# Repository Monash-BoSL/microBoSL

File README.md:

# microBoSL
This is a repository for the microBoSL motor controller

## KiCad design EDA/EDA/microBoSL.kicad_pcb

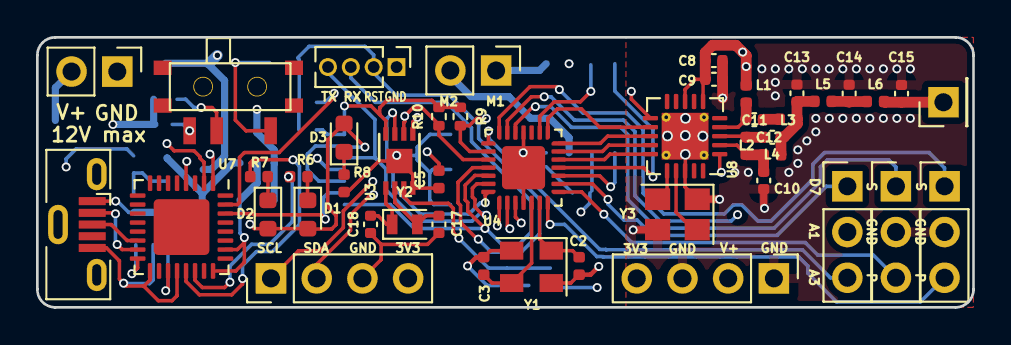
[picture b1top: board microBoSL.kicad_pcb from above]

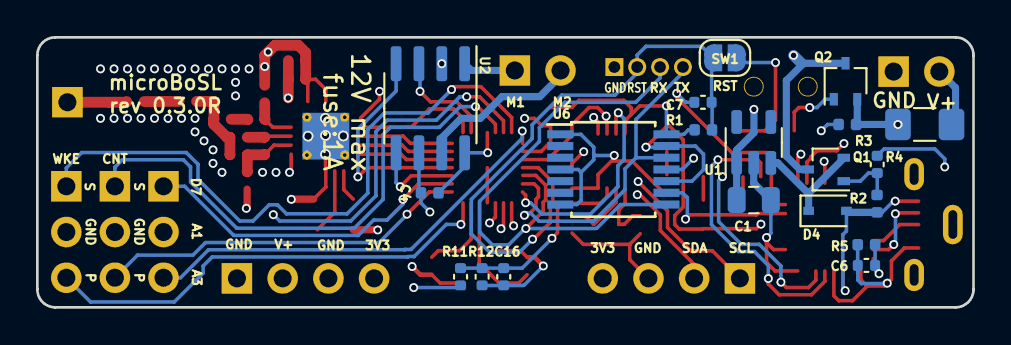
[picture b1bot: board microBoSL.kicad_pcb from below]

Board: 4 copper layers, 52.0 x 15.0 mm, 65 parts (20 on the bottom side), 58 nets.

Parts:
AE1: Antenna; PinHeader_1x01_P2.54mm_Vertical
C1: 2.2 μF; C_0805_2012Metric
C2, C3: 22 pF; C_0402_1005Metric
C4, C5, C6, C7, C9, C16: 100 nF; C_0402_1005Metric
C8: 100 pF; C_0402_1005Metric
C10, C12: 5.1 pF; C_0402_1005Metric
C11: 6.8 pF; C_0402_1005Metric
C13: 12 pF; C_0402_1005Metric
C14: 18 pF; C_0402_1005Metric
C15: 9.1 pF; C_0402_1005Metric
C17, C18: 15 pF; C_0402_1005Metric
D1, D2, D3: LED; LED_0603_1608Metric
D4: CUS08F30,H3F; D_SOD-323
F1: 1A; Fuse_1206_3216Metric_Pad1.42x1.75mm_HandSolder
J1, J4: Conn_01x04; PinHeader_1x04_P2.54mm_Vertical
J2, J6, J7: Conn_01x03; PinHeader_1x03_P2.54mm_Vertical
J3: Conn_01x04; PinHeader_1x04_P1.27mm_Vertical
J5: Conn_01x02; PinHeader_1x02_P2.54mm_Vertical
J8: USB_B_Micro; USB_Micro-B_Molex-105133-0001
J9: MOTOR_OUT; PinHeader_1x02_P2.54mm_Vertical
L1: 220 nH; L_0402_1005Metric
L2: 68 nH; L_0402_1005Metric
L3: 24 nH; L_0402_1005Metric
L4: 27 nH; L_0402_1005Metric
L5, L6: 12 nH; L_0402_1005Metric
Q1, Q2: DMP2165UW; SOT-323_SC-70
R1, R2, R3, R5, R9, R10: 10 kΩ; R_0402_1005Metric
R4, R11, R12: 4.7 MΩ; C_0402_1005Metric
R6, R7, R8: 3.3 kΩ; R_0402_1005Metric
SW1: RST; SolderJumper-2_P1.3mm_Open_RoundedPad1.0x1.5mm
SW2: EG1215AA
U1: TPS709A33DBVT; SOT-23-5
U2: ZXBM5210-S; SOIC-8_3.9x4.9mm_P1.27mm
U3: MCP7940N-xMNY; DFN-8-1EP_3x2mm_P0.5mm_EP1.36x1.46mm
U4: ATmega328-MMH; QFN-28-1EP_4x4mm_P0.45mm_EP2.4x2.4mm
U6: 74HC126PW-Q100; TSSOP-14_4.4x5mm_P0.65mm
U7: FT232RQ; QFN-32-1EP_5x5mm_P0.5mm_EP3.1x3.1mm
U8: Si4463; QFN-20-1EP_4x4mm_P0.5mm_EP2.6x2.6mm_ThermalVias
Y1: 8MHz; Crystal_SMD_EuroQuartz_MT-4Pin_3.2x2.5mm
Y2: 32.768 kHz; Crystal_SMD_2012-2Pin_2.0x1.2mm
Y3: 30 MHz; Crystal_SMD_Abracon_ABM8G-4Pin_3.2x2.5mm

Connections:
A1: J2.2, U4.20 (PC1)
A3: J2.3, U4.22 (PC3)
AND_RX: U6.9 (A3), U7.30 (TXD)
AND_TX: U6.11 (Y4), U7.2 (RXD)
D7: J2.1, U4.9 (PD7)
EN_RADIO: U4.2 (PD4), U8.1 (SDN)
GND: C1.2, C2.1, C3.1, C4.1, C5.2, C6.2, C8.2, C9.2, C10.2, C13.2, C14.2, C15.2, C16.2, C17.1, C18.1, J1.3, J3.1, J4.1, J4.3, J5.1, J6.2, J7.2, J8.5 (GND), R4.1, R5.2, R8.2, R12.2, SW1.1, SW2.1 (A), U1.2 (GND), U2.8 (GND), U3.4 (VSS), U3.9 (EP), U4.4 (GND), U4.18 (GND), U4.29 (GND), U6.1 (OE1), U6.4 (OE2), U6.7 (GND), U7.4 (GND), U7.17 (GND), U7.20 (GND), U7.24 (AGND), U7.26 (TEST), U8.18 (GND), U8.21 (GND), Y1.2, Y1.4, Y3.1, Y3.3
Hall_CNT_P: J6.3, U4.8 (PD6)
Hall_CNT_S: J6.1, U4.19 (PC0)
Hall_WKE_P: J7.3, U4.7 (PD5)
Hall_WKE_S: J7.1, U4.21 (PC2)
I_RADIO: U4.1 (PD3), U8.11 (~IRQ)
MFWD: U2.4 (FWD), U4.11 (PB1)
MISO: U4.14 (PB4), U8.13 (SDO)
MOSI: U4.13 (PB3), U8.14 (SDI)
MREV: U2.5 (REV), U4.10 (PB0)
unnamed: AE1.1 (A), C15.1, L6.2
unnamed: C2.2, U4.6 (XTAL2/PB7), Y1.1
unnamed: C3.2, U4.5 (XTAL1/PB6), Y1.3
unnamed: C7.2, U7.31 (DTR)
unnamed: C10.1, L2.1, L4.1, U8.2 (RXp)
unnamed: C11.1, L3.1
unnamed: C11.2, L1.2, U8.4 (TX)
unnamed: C12.1, C13.1, L3.2, L4.2, L5.1
unnamed: C12.2, L2.2, U8.3 (RXn)
unnamed: C14.1, L5.2, L6.1
unnamed: C16.1, R11.2, R12.1, U3.3 (VBAT)
unnamed: C17.2, U3.2 (X2), Y2.2
unnamed: C18.2, U3.1 (X1), Y2.1
unnamed: D1.1 (K), R6.1
unnamed: D2.1 (K), R7.1
unnamed: D3.1 (K), R8.1
unnamed: D4.1 (K), Q1.2 (S), U1.3 (IN)
unnamed: F1.2, J5.2
unnamed: J9.1, U2.1 (OUT1)
unnamed: J9.2, U2.7 (OUT2)
unnamed: Q1.1 (G), R2.1, R4.2
unnamed: Q2.1 (G), SW2.2 (B)
unnamed: R3.1, SW2.3 (C)
unnamed: R6.2, U7.22 (CBUS0)
unnamed: R7.2, U7.21 (CBUS1)
unnamed: U8.16 (XOUT), Y3.2
unnamed: U8.17 (XIN), Y3.4
RTC_I: U3.7 (MFP), U4.28 (PD2)
SCL: J1.1, R10.1, U3.6 (SCL), U4.24 (PC5)
SCLK: U4.15 (PB5), U8.12 (SCLK)
SDA: J1.2, R9.2, U3.5 (SDA), U4.23 (PC4)
SS: U4.12 (PB2), U8.15 (~SEL)
TLL_RST: C7.1, J3.2, R1.2, SW1.2, U4.25 (~RESET/PC6)
TLL_RX: J3.3, U4.26 (PD0), U6.8 (Y3)
TLL_TX: J3.4, U4.27 (PD1), U6.12 (A4)
TTL_3.3V: C6.1, D1.2 (A), D2.2 (A), D3.2 (A), R5.1, U6.10 (OE3), U6.13 (OE4), U7.1 (VCCIO), U7.16 (3V3OUT)
USB_DM: J8.2 (D-), U7.15 (USBD-)
USB_DP: J8.3 (D+), U7.14 (USBD+)
USB_V: D4.2 (A), J8.1 (VBUS), R2.2, U7.19 (VCC)
VBAT: C5.1, Q1.3 (D), Q2.3 (D), U2.2 (VM)
VPP: F1.1, J4.2, Q2.2 (S), R3.2, R11.1
V_3.3: C1.1, C4.2, C8.1, C9.1, J1.4, J4.4, L1.1, R1.1, R9.1, R10.2, U1.1 (OUT), U2.3 (VDD), U2.6 (VREF), U3.8 (VCC), U4.3 (VCC), U4.16 (AVCC), U6.14 (VCC), U8.6 (VDD), U8.8 (VDD)

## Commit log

2021-06-24 initial commit of movement of microBoSL to indepedent repository
2021-06-25 fixed o-ring circuit
2021-12-15 update of BOM
2022-05-17 updated kicad to rev 6.0
2022-05-17 rebase for adding wireless to microbosl
2022-05-17 added Si4463 radio module
2022-05-17 moved location on pcb of si4463
2022-06-09 finalised schematic for radio microbosl
2022-06-09 laying out pcb
2022-06-09 more work on PCB layout
2022-06-15 finished component placement
2022-06-15 added BOM and finished most layout
2022-06-15 adding silkscreen
2022-06-20 finished layout of pcb
2022-06-20 microBoSL rev 0.3.0R release
2022-07-07 added code for si4463 radio
